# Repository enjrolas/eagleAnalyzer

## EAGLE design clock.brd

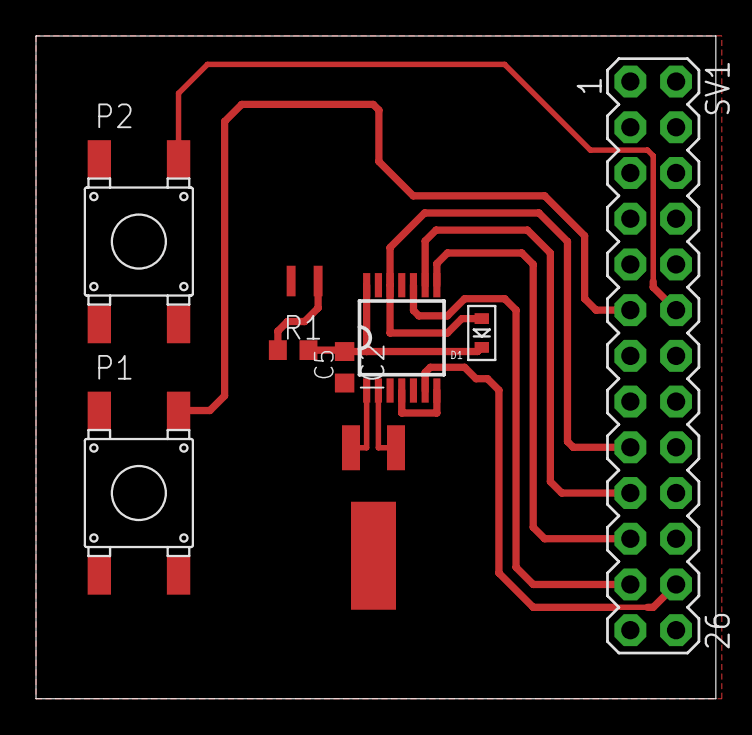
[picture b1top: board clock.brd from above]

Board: 2 copper layers, 37.8 x 36.8 mm, 9 parts (0 on the bottom side), 12 nets.

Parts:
C5: 100n; C0603K
D1: SOD-523
IC2: PCF2123TSSOP14; TSSOP14
P1, P2: FSM4JSMA-SMD
R1: 1k; R0603
SV1: MA13-2
U$1: DCK-3R3E224U-E; SUPCAP-E
X2: CRYSTALTFORK_SMD; TFORK_SMD

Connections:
+3V3: D1.A, IC2.12, SV1.17
CE0: IC2.6, SV1.24
GND: C5.1, IC2.4, IC2.7, P1.P$1, P2.P$1, SV1.9, U$1.-
GPIO0: P1.P$3, SV1.11
GPIO1: P2.P$3, SV1.12
MISO: IC2.8, SV1.21
MOSI: IC2.9, SV1.19
unnamed: R1.1, U$1.+
unnamed: IC2.2, X2.3
unnamed: IC2.1, X2.2
SCLK: IC2.10, SV1.23
VRTC: C5.2, D1.K, IC2.14, R1.2

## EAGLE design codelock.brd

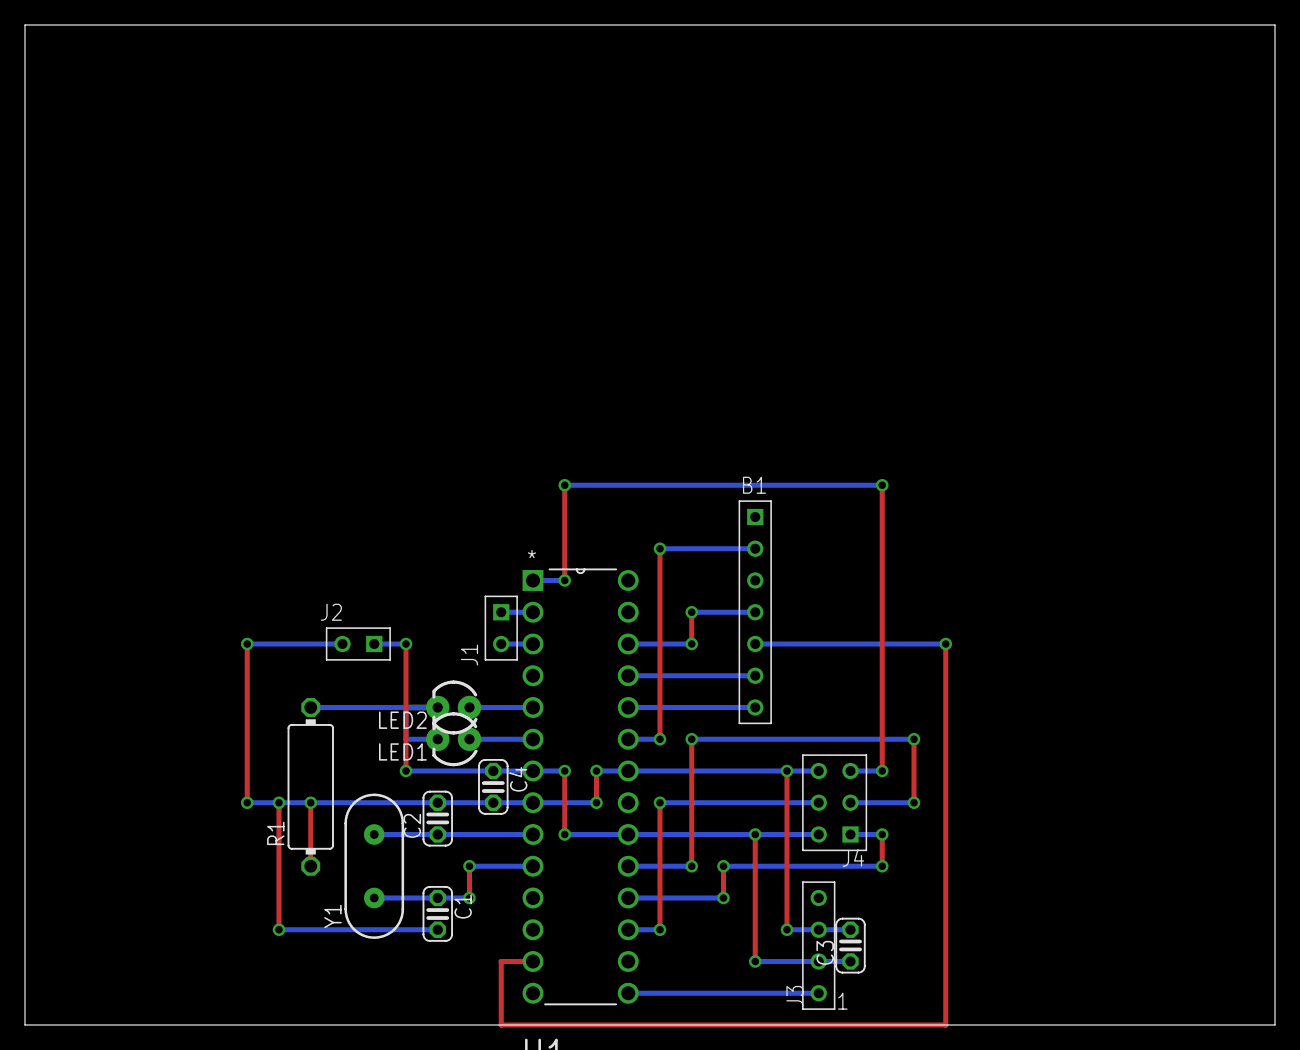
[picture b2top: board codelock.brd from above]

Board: 2 copper layers, 100.0 x 80.0 mm, 14 parts (0 on the bottom side), 21 nets.

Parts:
B1: KEYPAD12
C1, C2: 22pF; C025-024X044
C3, C4: C025-024X044
J1, J2: 1BY2THROUGHHOLE; 1BY2
J3: 4PIN2.54MM1X4TH; 2.54MM1X4TH
J4: ISP; DUALHEAD_TH_6
LED1, LED2: LED3MM
R1: 330R; V234/12
U1: ATMEGA168-20PU; DIP254P762X457-28
Y1: HC49US

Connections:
+3V3: C3.1, C4.1, J2.1, J3.2, J4.2, U1.7, U1.20
C0: B1.C0, U1.11
C1: B1.C1, U1.12
C2: B1.C2, U1.13
GND: C1.2, C2.2, C3.2, C4.2, J2.2, J3.3, J4.6, R1.1, U1.8, U1.22
LED_GREEN: LED2.A, U1.5
LED_RED: LED1.A, U1.6
unnamed: LED1.K, LED2.K, R1.2
unnamed: J4.4, U1.17
unnamed: J4.1, U1.18
unnamed: J4.3, U1.19
NRESET: J4.5, U1.1
R0: B1.R0, U1.23
R1: B1.R1, U1.24
R2: B1.R2, U1.25
R3: B1.R3, U1.26
RX: J1.1, U1.2
SERVO: J3.1, U1.15
TOSC1: C2.1, U1.9, Y1.2
TOSC2: C1.1, U1.10, Y1.1
TX: J1.2, U1.3

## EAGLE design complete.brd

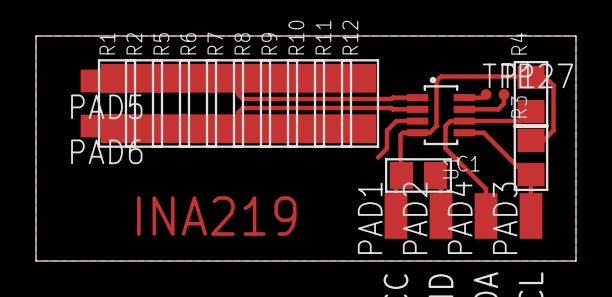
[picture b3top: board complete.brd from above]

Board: 2 copper layers, 30.0 x 12.5 mm, 22 parts (0 on the bottom side), 8 nets.

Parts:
C1: 0.1µF; 0805
PAD1, PAD2, PAD3, PAD4, PAD5, PAD6: SMD1,27-2,54
R1, R2, R5, R6, R7, R8, R9, R10, R11, R12: 1R; 1206
R3, R4: 10K; 0805
TP1, TP27: TPTP06R; TP06R
U1: INA219BIDCNT; SOT23-8

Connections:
GND: C1.2, PAD2.1, U1.3
unnamed: TP27.TP, U1.7
unnamed: TP1.TP, U1.8
SCL: PAD3.1, R3.1, U1.5
SDA: PAD4.1, R4.1, U1.6
VCC: C1.1, PAD1.1, R3.2, R4.2, U1.4
VIN+: PAD5.1, R1.2, R2.2, R5.2, R6.2, R7.2, R8.2, R9.2, R10.2, R11.2, R12.2, U1.1
VIN-: PAD6.1, R1.1, R2.1, R5.1, R6.1, R7.1, R8.1, R9.1, R10.1, R11.1, R12.1, U1.2

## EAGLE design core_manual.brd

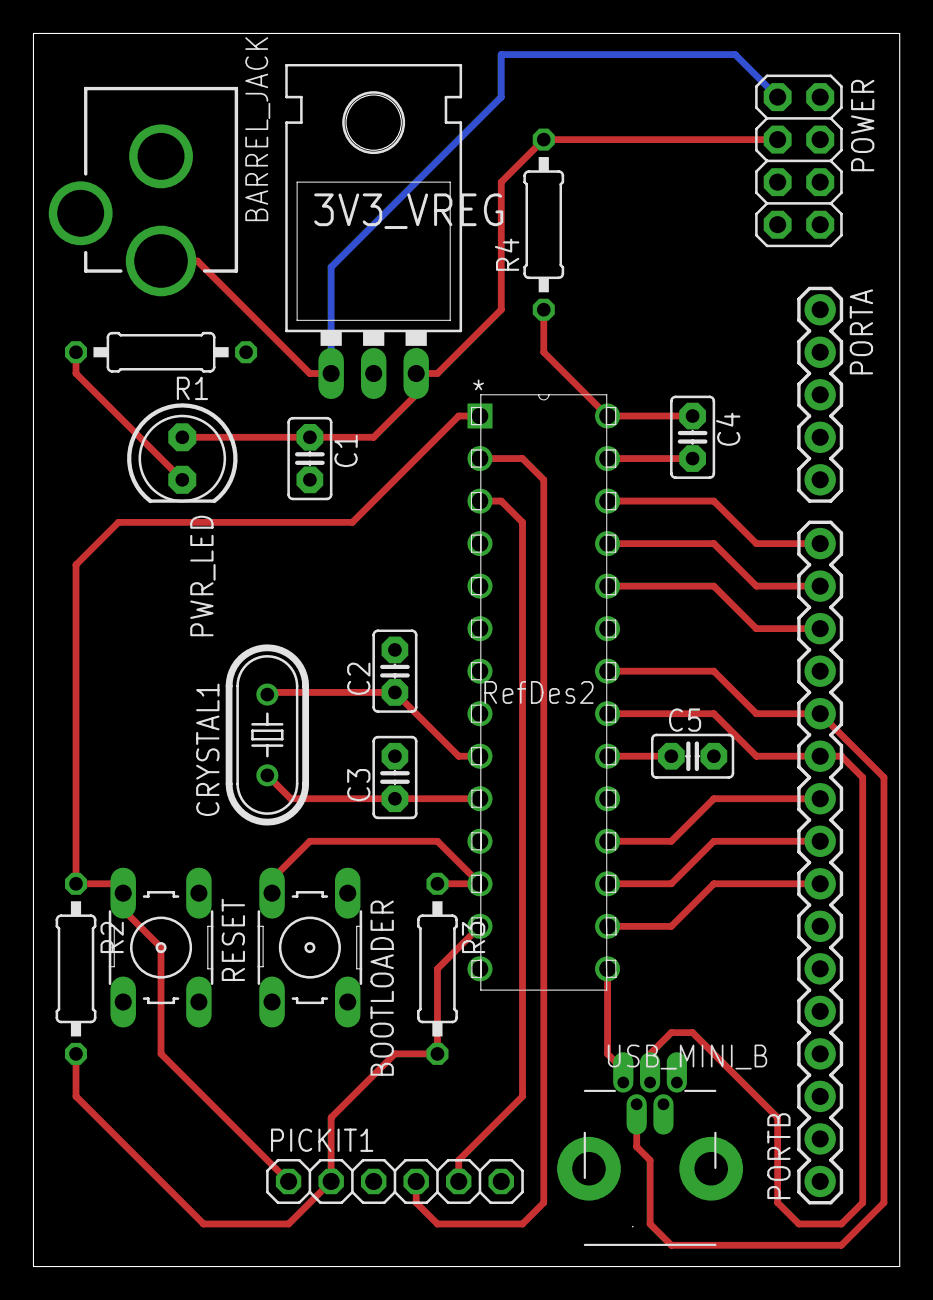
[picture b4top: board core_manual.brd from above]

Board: 2 copper layers, 51.7 x 73.6 mm, 21 parts (0 on the bottom side), 28 nets.

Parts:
3V3_VREG: 3.3; TO-220-ALT
BARREL_JACK: DCJACK_2MM_PTH
BOOTLOADER: B3F-10XX
C1, C4, C5: .1uF; C2.5-2
C2, C3: 22pF; C2.5-2
CRYSTAL1: 20M; HC49U-V
PICKIT1: 1X06
PORTA: 1X05
PORTB: M16PTH; 1X16
POWER: 2X04
PWR_LED: LED5MM
R1: 47; 0207/10
R2, R3, R4: 10K; 0207/10
RESET: B3F-10XX
U1: PIC32MX230F064B-; SPDIP28_300MC
USB_MINI_B: USB-MINIB-THM-MOLEX

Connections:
+3V3: 3V3_VREG.OUT, C1.1, PICKIT1.2, POWER.3, POWER.4, PWR_LED.A, R2.2, R3.2, R4.2, U1.13, U1.23
+5V: 3V3_VREG.IN, BARREL_JACK.PWR, POWER.1, POWER.2
AVDD: C4.1, R4.1, U1.28
AVSS: C4.2, U1.27
D+: PORTB.11, U1.21, USB_MINI_B.D+
D-: PORTB.12, U1.22, USB_MINI_B.D-
GND: 3V3_VREG.GND, BARREL_JACK.GND, BARREL_JACK.GNDBREAK, BOOTLOADER.1, C1.2, C2.2, C3.2, C5.2, PICKIT1.3, POWER.5, POWER.6, POWER.7, POWER.8, R1.1, RESET.1, U1.8, U1.19, USB_MINI_B.GND
MCLR: PICKIT1.1, R2.1, RESET.3, U1.1
unnamed: PWR_LED.K, R1.2
OSC1: C2.1, CRYSTAL1.2, PORTA.3, U1.9
OSC2: C3.1, CRYSTAL1.1, PORTA.4, U1.10
RA0: PICKIT1.4, PORTA.1, U1.2
RA1: PICKIT1.5, PORTA.2, U1.3
RA4: BOOTLOADER.3, PORTA.5, R3.1, U1.12
RB0: PORTB.1, U1.4
RB1: PORTB.2, U1.5
RB2: PORTB.3, U1.6
RB3: PORTB.4, U1.7
RB4: PORTB.5, U1.11
RB5: PORTB.6, U1.14
RB7: PORTB.8, U1.16
RB8: PORTB.9, U1.17
RB9: PORTB.10, U1.18
RB13: PORTB.14, U1.24
RB14: PORTB.15, U1.25
RB15: PORTB.16, U1.26
VBUS: U1.15, USB_MINI_B.VBUS
VCAP: C5.1, U1.20

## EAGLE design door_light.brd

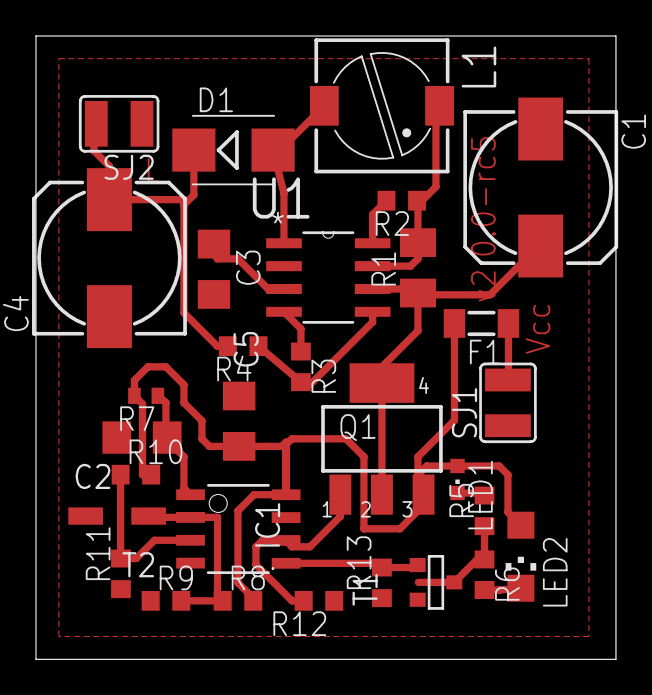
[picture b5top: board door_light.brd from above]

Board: 2 copper layers, 32.2 x 34.6 mm, 30 parts (0 on the bottom side), 18 nets.

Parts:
C1, C4: 100uF; 153CLV-0810
C2, C5: 100nF; C1206
C3: 1.5nF; C1206
D1: MBRS140T3G; SMB
F1: SD075-16 (F750mA); MINI_MELF-0204W
IC1: TINY13-20SSU; 8S1
L1: 150uH; PIS2816
LED1: RED; CHIPLED_0603
LED2: IR; CHIPLED_1206
Q1: BSP250; SOT223
R1: 0.22R; M1206
R2: 180R; R0603
R3: 2.7kR; R0603
R4: 24kR; R0603
R5, R6: 470R; R0603
R7: 10kR; R0402
R8, R10: 10kR; R0603
R9, R11: 2.9kR; R0603
R12, R13: 100kR; R0603
SJ1: PWR; SJW
SJ2: LIGHT; SJW
T1: n-mosfet; SOT-23
T2: KP-3216P3C; OPTO-TRANS-SIEMENS_BP103
U1: MC33063ADE4; SOIC127P600X175-8N

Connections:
0V: C1.-, C2.2, C3.2, C4.-, C5.2, IC1.4, R3.1, R9.1, R11.1, R12.1, R13.1, SJ1.1, SJ2.1, T1.2, T2.EMITER, U1.2, U1.4
+4.1V: C5.1, F1.2, IC1.8, LED1.A, LED2.A, Q1.3, R7.2, R8.2, R10.2
+12V: C4.+, D1.C, R4.2, SJ2.2
unnamed: LED1.C, R5.2
unnamed: LED2.C, R6.2
unnamed: C1.+, Q1.2, Q1.4, R1.1, U1.6
unnamed: R5.1, R6.1, T1.1
unnamed: F1.1, SJ1.2
unnamed: C2.1, IC1.1, R7.1
unnamed: C3.1, U1.3
unnamed: D1.A, L1.2, U1.1
unnamed: IC1.2, R8.1, R9.2, T2.COLLECTOR
unnamed: IC1.6, Q1.1, R12.2
unnamed: IC1.5, R13.2, T1.3
unnamed: R2.2, U1.8
unnamed: L1.1, R1.2, R2.1, U1.7
unnamed: IC1.3, R10.1, R11.2
unnamed: R3.2, R4.1, U1.5

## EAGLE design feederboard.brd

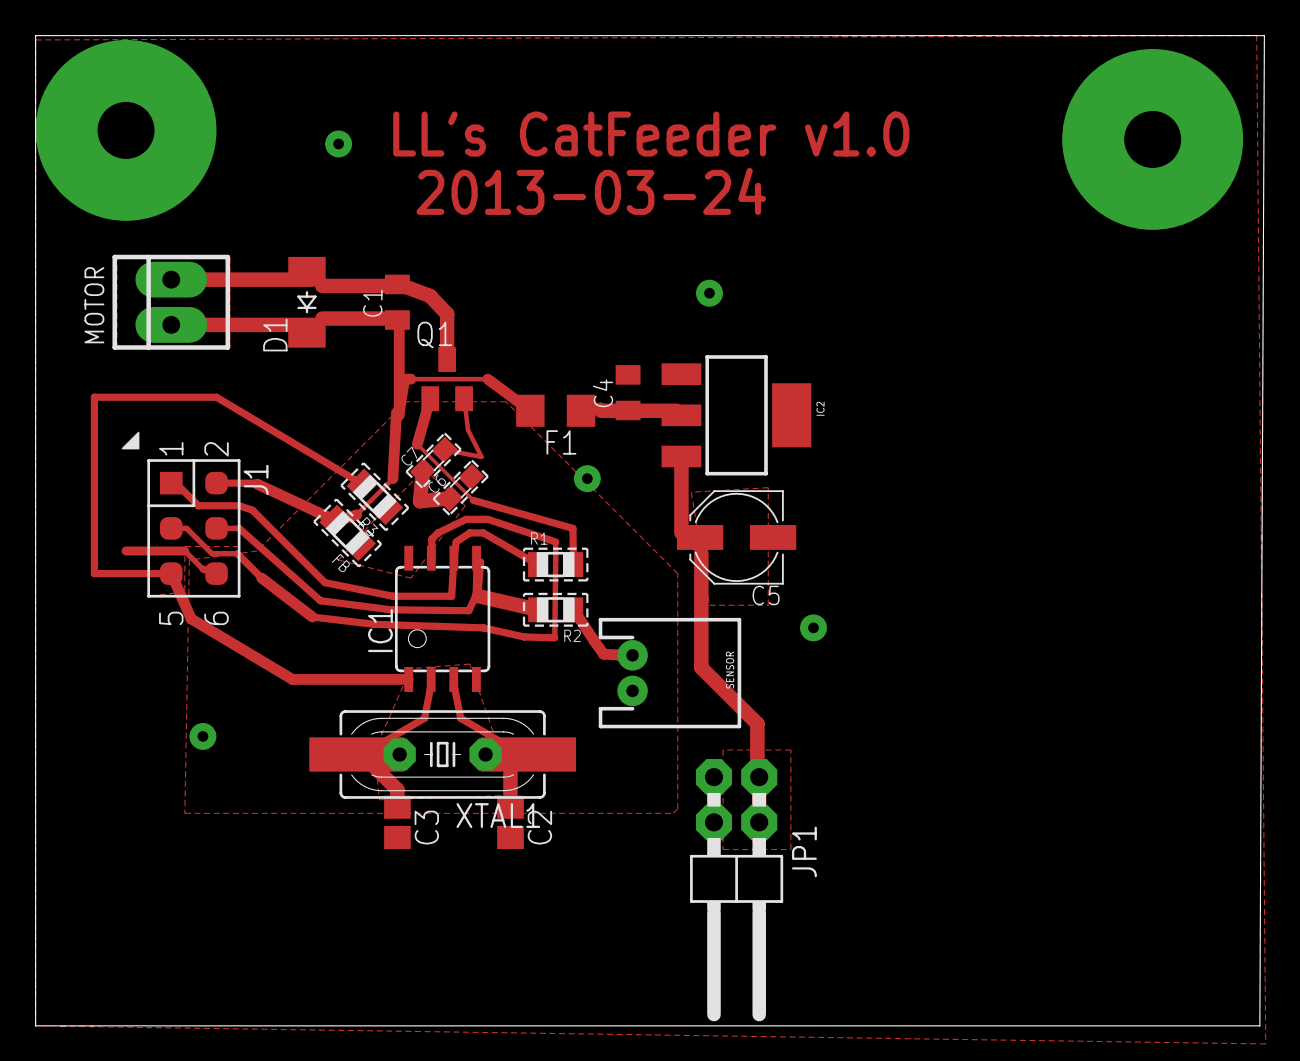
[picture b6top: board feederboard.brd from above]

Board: 2 copper layers, 69.0 x 55.6 mm, 21 parts (0 on the bottom side), 14 nets.

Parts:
C1: 1uf; C0805K
C2, C3: C0805
C4: 10uF; C0805K
C5: 100uF; PANASONIC_C
C6: .1uF; C0603
C7: 1uF; C0603
D1: CGRM4001-G; SOD-123_MINI-SMA
F1: R1206
FB: R0805
IC1: TINY13V-10SU; 8S2
IC2: SOT223
J1: CON_HEADER_PRG_AVR_ICSP_ETCH; HEADER_PRG_2X03_ETCH
JP1: 2X02/90
MOTOR: 22-23-2021
Q1: SOT23
R1: 470; R0805
R2: 10k; R0805
R3: 100k; R0805
SENSOR: JST-2-PTH
XTAL1: HC-49U-OR-DIP

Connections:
5V: C1.1, D1.C, F1.2, FB.2, J1.2, MOTOR.1
GND: C2.2, C3.2, C4.2, C5.-, C6.2, C7.2, IC1.4, IC2.1, J1.6, JP1.3, JP1.4, Q1.2, SENSOR.2
MISO: IC1.6, J1.1, R1.1
MOSI: IC1.5, J1.4, R2.2
unnamed: C2.1, IC1.3, XTAL1.1
unnamed: C3.1, IC1.2, XTAL1.2
unnamed: C1.2, D1.A, MOTOR.2, Q1.3
unnamed: Q1.1, R1.2
RST: IC1.1, J1.5, R3.2
SCK: IC1.7, J1.3
SWITCH: R2.1, SENSOR.1
VCC: C6.1, C7.1, FB.1, IC1.8, R3.1
VIN: C5.+, IC2.3, JP1.1, JP1.2
VR-OUTSM: C4.1, F1.1, IC2.2

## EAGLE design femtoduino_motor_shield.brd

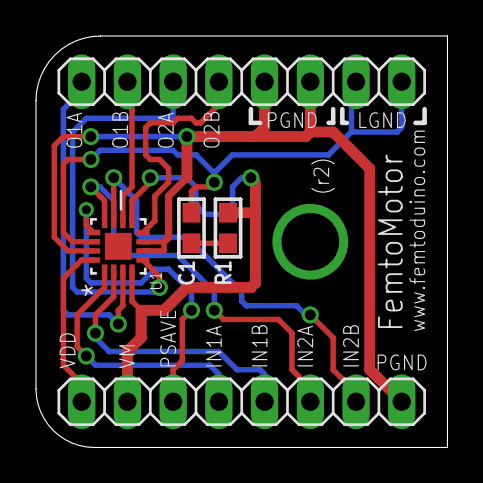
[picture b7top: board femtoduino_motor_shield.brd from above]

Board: 2 copper layers, 22.9 x 22.9 mm, 6 parts (1 on the bottom side), 13 nets.

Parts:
C1: 0.01uF; 0603
JP1, JP2: 1X08
R1: 10k; 0603
U1: H-BRIDGE; QFN50P300X300X100-17N
U$1: OSHW_FILLX150_NOTEXT

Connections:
GND: C1.1, C1.2, JP2.7, JP2.8, R1.2, U1.14
IN1A: JP1.4, U1.1
IN1B: JP1.5, U1.2
IN2A: JP1.6, U1.12
IN2B: JP1.7, U1.11
OUT1A: JP2.1, U1.3
OUT1B: JP2.2, U1.10
OUT2A: JP2.3, U1.5
OUT2B: JP2.4, U1.8
PGND: JP1.8, JP2.5, JP2.6, U1.6, U1.7, U1.15
PSAVE: JP1.3, U1.13
VDD: JP1.1, U1.16
VM1: JP1.2, R1.1, U1.4, U1.9

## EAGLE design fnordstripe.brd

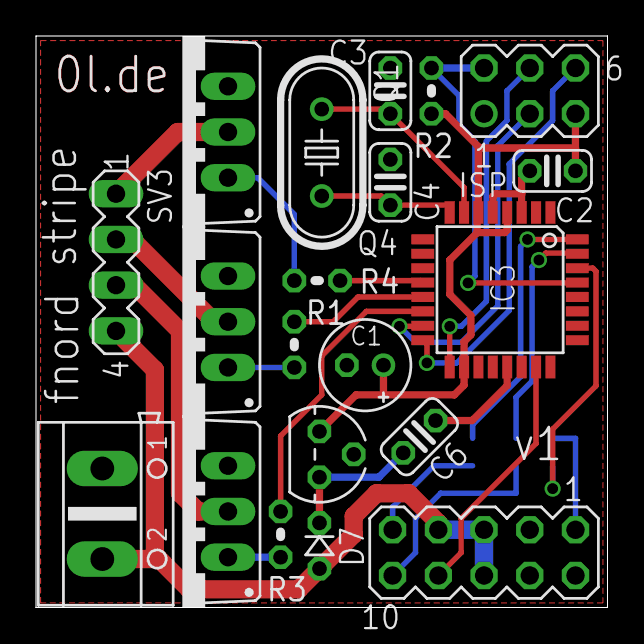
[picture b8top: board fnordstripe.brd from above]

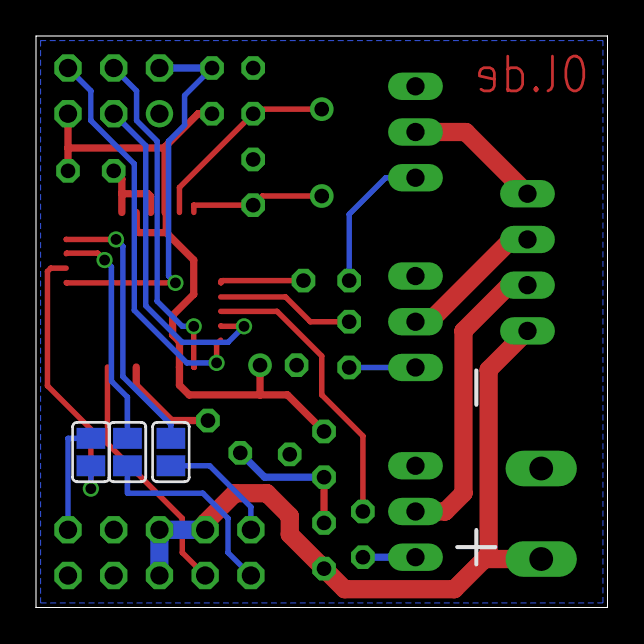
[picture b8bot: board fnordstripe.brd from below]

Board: 2 copper layers, 31.8 x 31.8 mm, 23 parts (3 on the bottom side), 26 nets.

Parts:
BUS: MA05-2
C1: 47uF; E2-5
C2, C6: 100n; C025-024X044
C3, C4: 33p; C025-024X044
D7: D-2.5
IC2: 78L05Z; TO92
IC3: MEGA8-AI; TQFP32-08
ISP: MA03-2
Q1: 16MHz; HC49U-V
Q2, Q3, Q4: IRF540; TO220BV
R1, R3, R4: 50; 0204V
R2: 2k2; 0204V
SJ1, SJ2, SJ3: SJ
SV3: MA04-1
X1: AK500/2

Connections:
+5V: C1.+, C2.1, IC2.1, IC3.4, IC3.6, IC3.18, ISP.5, R2.1
+12V: BUS.5, BUS.6, BUS.7, D7.A, SV3.4, X1.2
ADC0: BUS.8, IC3.23
BLUE: IC3.14, R3.2
BUSINT: BUS.9, SJ3.2
DATA1: BUS.10, SJ2.2
DATA2: BUS.1, SJ1.2
GND: BUS.2, BUS.3, BUS.4, C1.-, C2.2, C3.2, C4.2, C6.2, IC2.2, IC3.3, IC3.5, IC3.21, ISP.1, Q2.S, Q3.S, Q4.S, X1.1
GREEN: IC3.13, R1.2
INT0: IC3.32, SJ3.1
MISO: IC3.16, ISP.6
MOSI: IC3.15, ISP.3
unnamed: Q2.G, R1.1
unnamed: Q3.G, R3.1
unnamed: Q3.D, SV3.3
unnamed: Q4.G, R4.2
unnamed: Q2.D, SV3.2
unnamed: Q4.D, SV3.1
unnamed: C6.1, D7.C, IC2.3
RED: IC3.12, R4.1
RST: IC3.29, ISP.2, R2.2
RX: IC3.30, SJ1.1
SCK: IC3.17, ISP.4
TX: IC3.31, SJ2.1
XTAL1: C3.1, IC3.7, Q1.1
XTAL2: C4.1, IC3.8, Q1.2

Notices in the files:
parts and their libraries:
SparkFun: Licensing: CC v3.0 Share-Alike You are welcome to use this library for commercial purposes.
microbuilder: This work is placed in the public domain, and may be freely used for commercial and non-commercial work with the following conditions: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
